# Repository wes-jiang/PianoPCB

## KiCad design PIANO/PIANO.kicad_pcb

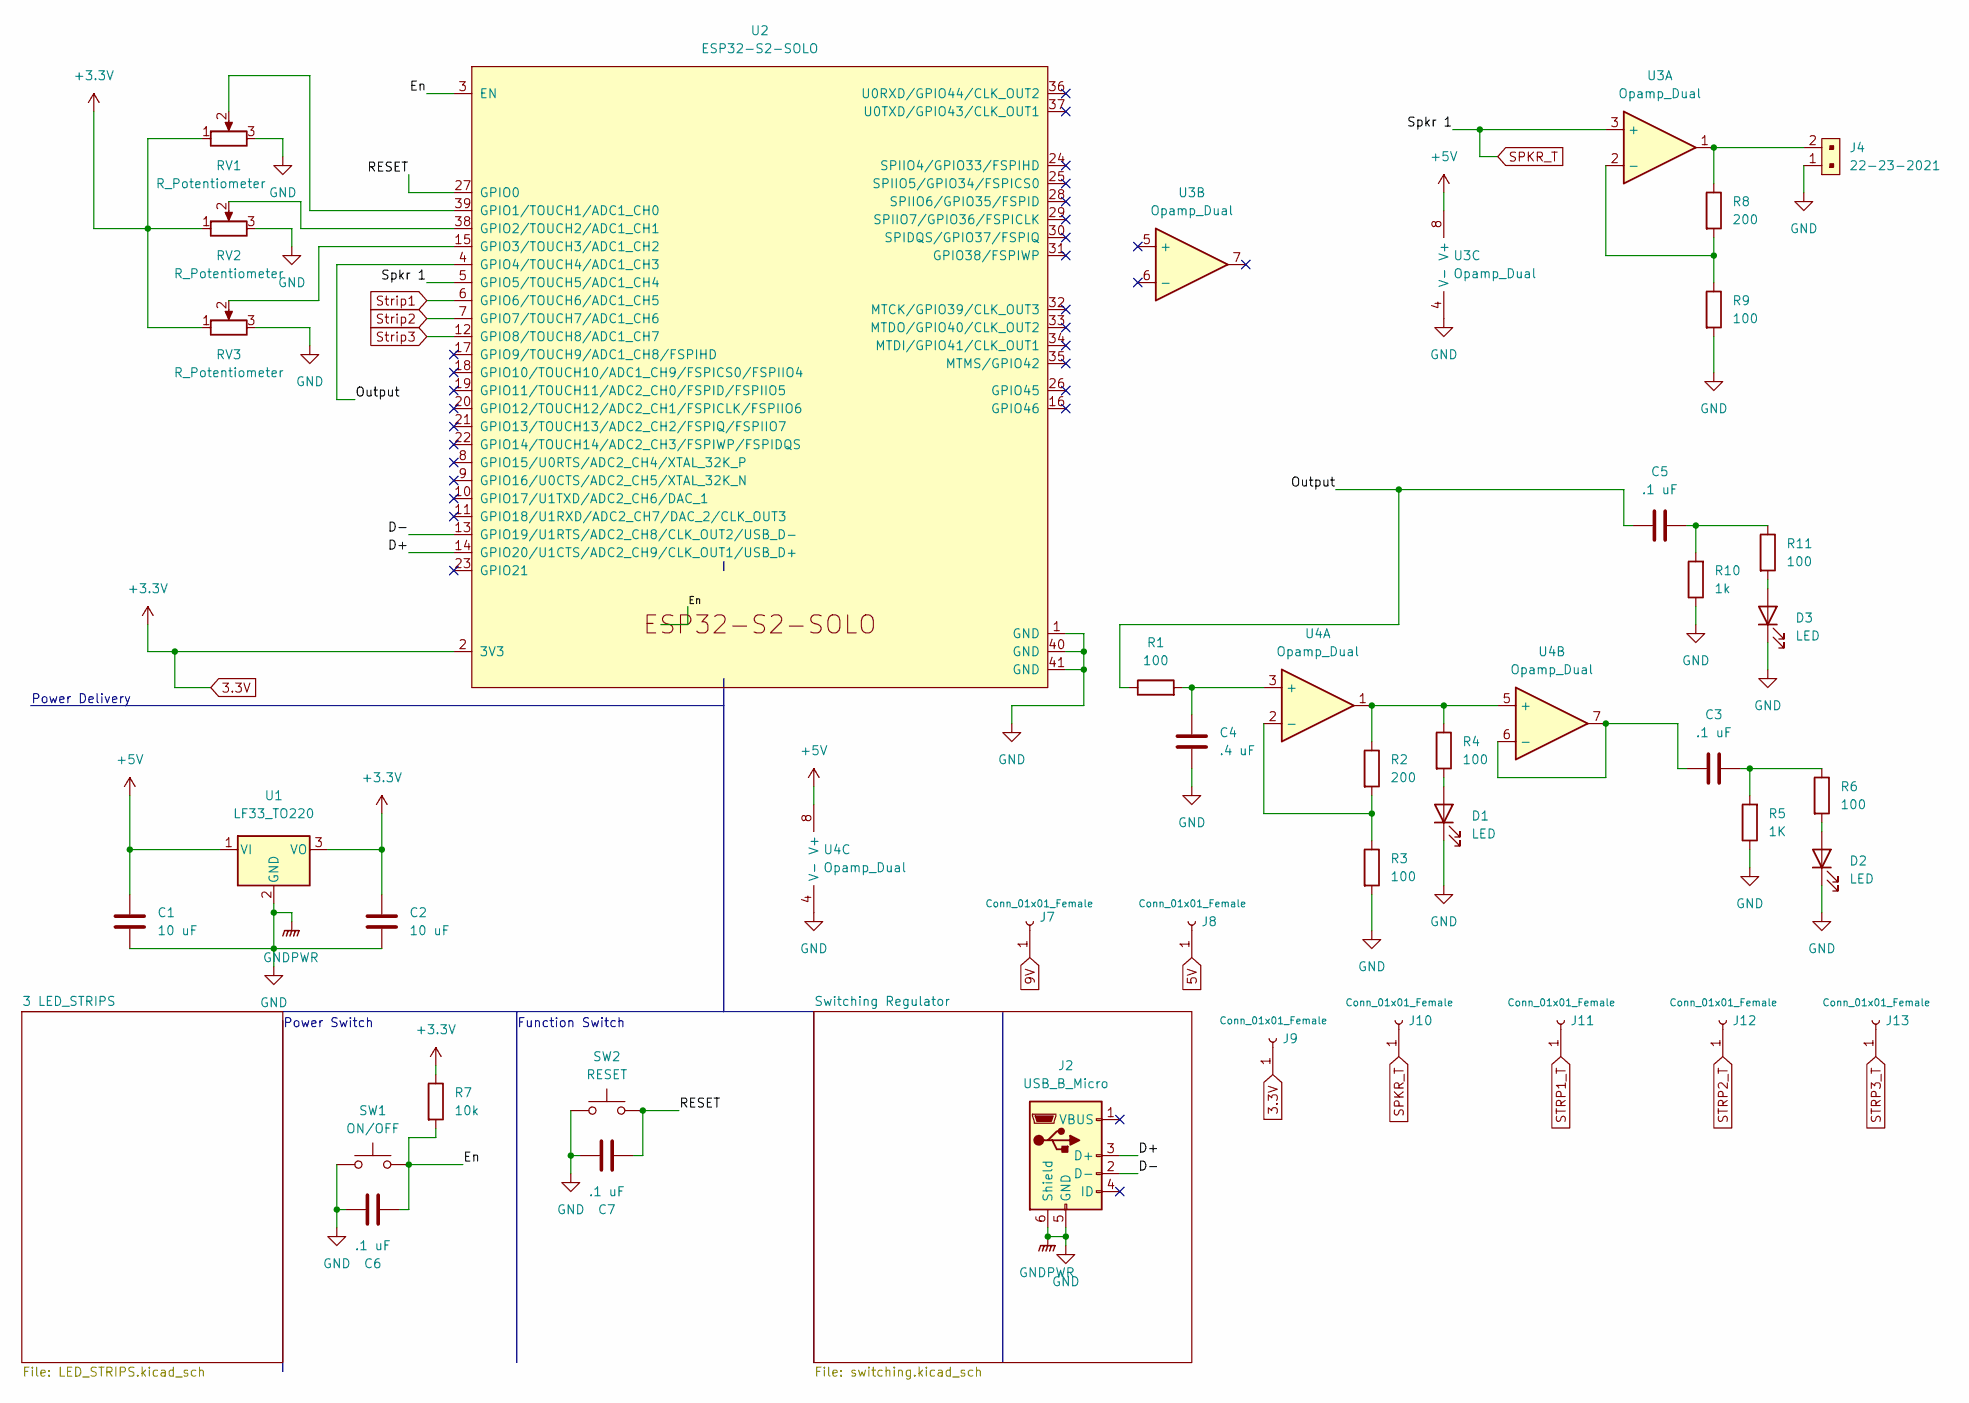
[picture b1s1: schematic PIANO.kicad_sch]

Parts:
C1, C2: 10 uF; C_0805_2012Metric
C3, C5, C6, C7: .1 uF; C_0603_1608Metric
C4: .4 uF; C_0603_1608Metric
D1, D2, D3: LED; LED_D5.0mm-3
J2: USB_B_Micro; USB_Micro-B_GCT_USB3076-30-A
J4: 22-23-2021; PinHeader_1x02_P2.54mm_Vertical; MPN 22-23-2021; Digi-Key_PN WM4200-ND
J7, J8, J9, J10, J11, J12, J13: Conn_01x01_Female; PinHeader_1x01_P2.54mm_Vertical
R1, R3, R4, R6, R9, R11: 100; R_0603_1608Metric
R2, R8: 200; R_0603_1608Metric
R5: 1K; R_0805_2012Metric
R7: 10k; R_0805_2012Metric
R10: 1k; R_0805_2012Metric
RV1, RV2, RV3: R_Potentiometer; Potentiometer_ACP_CA9-V10_Vertical
SW1: ON/OFF; SW_DPDT_CK_JS202011JCQN
SW2: RESET; SW_DPDT_CK_JS202011JCQN
U1: LF33_TO220; TO-220-3_Vertical
U2: ESP32-S2-SOLO
U3, U4: Opamp_Dual; SOIC127P600X175-8N

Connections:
3.3V: C2.1, J9.1, R7.1, RV1.1, RV2.1, RV3.1, U1.3 (VO), U2.2 (3V3)
5V: C1.1, J8.1, U1.1 (VI), U3.8 (V+), U4.8 (V+); also elsewhere on the board
9V: J7.1; also elsewhere on the board
/D+: J2.3 (D+), U2.14 (GPIO20/U1CTS/ADC2_CH9/CLK_OUT1/USB_D+)
/D-: J2.2 (D-), U2.13 (GPIO19/U1RTS/ADC2_CH8/CLK_OUT2/USB_D-)
/En: C6.2, R7.2, SW1.2, U2.3 (EN)
/IO0: C7.2, SW2.2, U2.27 (GPIO0)
/Output: C5.1, R1.1, U2.4 (GPIO4/TOUCH4/ADC1_CH3)
GND: C1.2, C2.2, C4.2, C6.1, C7.1, D1.1 (K), D2.1 (K), D3.1 (K), J2.5 (GND), J2.6 (Shield), J4.1, R3.2, R5.1, R9.2, R10.1, RV1.3, RV2.3, RV3.3, SW1.1, SW2.1, U1.2 (GND), U2.1 (GND), U2.40 (GND), U2.41 (GND), U3.4 (V-), U4.4 (V-); also elsewhere on the board
unnamed: C3.1, U4.6 (-), U4.7
unnamed: C3.2, R5.2, R6.1
unnamed: C4.1, R1.2, U4.3 (+)
unnamed: C5.2, R10.2, R11.1
unnamed: D1.2 (A), R4.2
unnamed: D2.2 (A), R6.2
unnamed: D3.2 (A), R11.2
unnamed: J4.2, R8.1, U3.1
unnamed: R2.1, R4.1, U4.1, U4.5 (+)
unnamed: R2.2, R3.1, U4.2 (-)
unnamed: R8.2, R9.1, U3.2 (-)
unnamed: RV1.2, U2.39 (GPIO1/TOUCH1/ADC1_CH0)
unnamed: RV2.2, U2.38 (GPIO2/TOUCH2/ADC1_CH1)
unnamed: RV3.2, U2.15 (GPIO3/TOUCH3/ADC1_CH2)
SPKR_T: J10.1, U2.5 (GPIO5/TOUCH5/ADC1_CH4), U3.3 (+)
STRP2_T: J12.1, U2.7 (GPIO7/TOUCH7/ADC1_CH6); also elsewhere on the board
STRP3_T: J13.1, U2.12 (GPIO8/TOUCH8/ADC1_CH7); also elsewhere on the board
Strip1: J11.1, U2.6 (GPIO6/TOUCH6/ADC1_CH5); also elsewhere on the board

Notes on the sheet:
Power Delivery
Power Switch
Function Switch

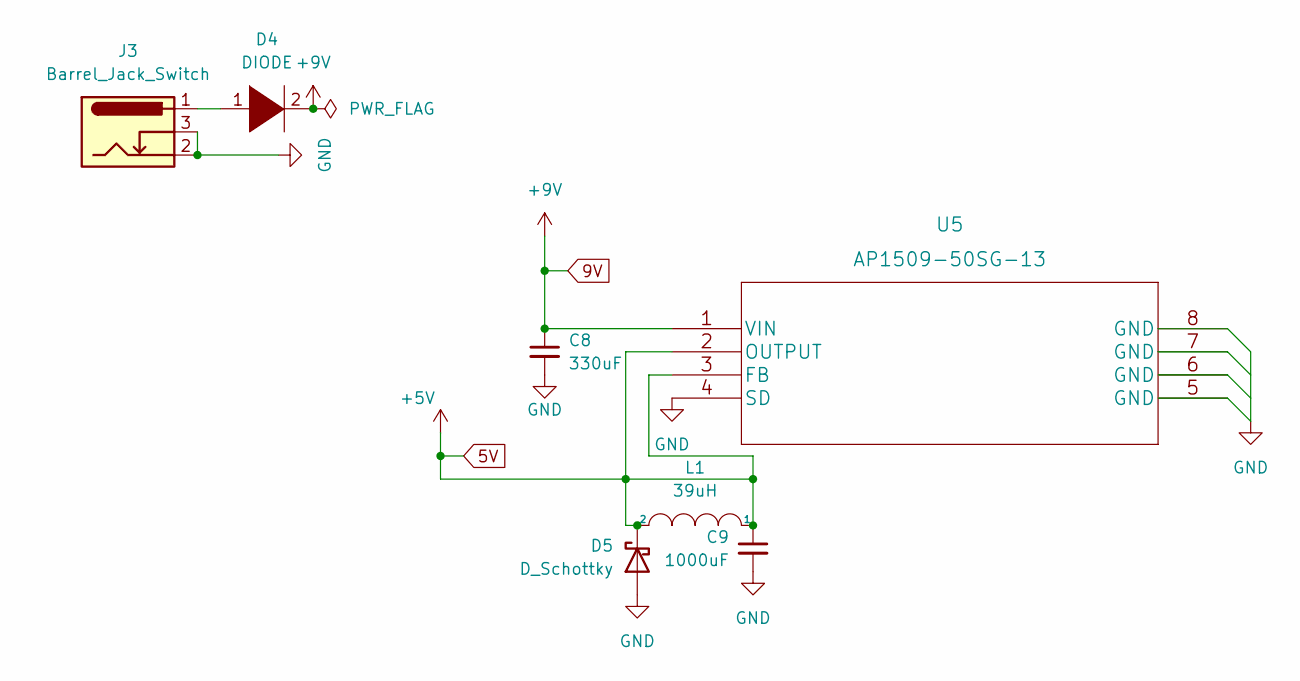
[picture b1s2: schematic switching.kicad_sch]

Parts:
C8: 330uF; C_1210_3225Metric
C9: 1000uF; C_Radial_D10.0mm_H16.0mm_P5.00mm
D4: DIODE; D_SOD-123F
D5: D_Schottky; D_SOD-123F
J3: Barrel_Jack_Switch; BarrelJack_Horizontal
L1: 39uH; L_10.4x10.4_H4.8
U5: AP1509-50SG-13; SOIC-8_3.9x4.9mm_P1.27mm

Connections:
5V: C9.1, D5.1 (K), L1.1, L1.2, U5.2 (OUTPUT), U5.3 (FB); also elsewhere on the board
9V: C8.1, D4.2 (A), U5.1 (VIN); also elsewhere on the board
GND: C8.2, C9.2, D5.2 (A), J3.2, J3.3, U5.4 (SD), U5.5 (GND), U5.6 (GND), U5.7 (GND), U5.8 (GND); also elsewhere on the board
unnamed: D4.1 (K), J3.1

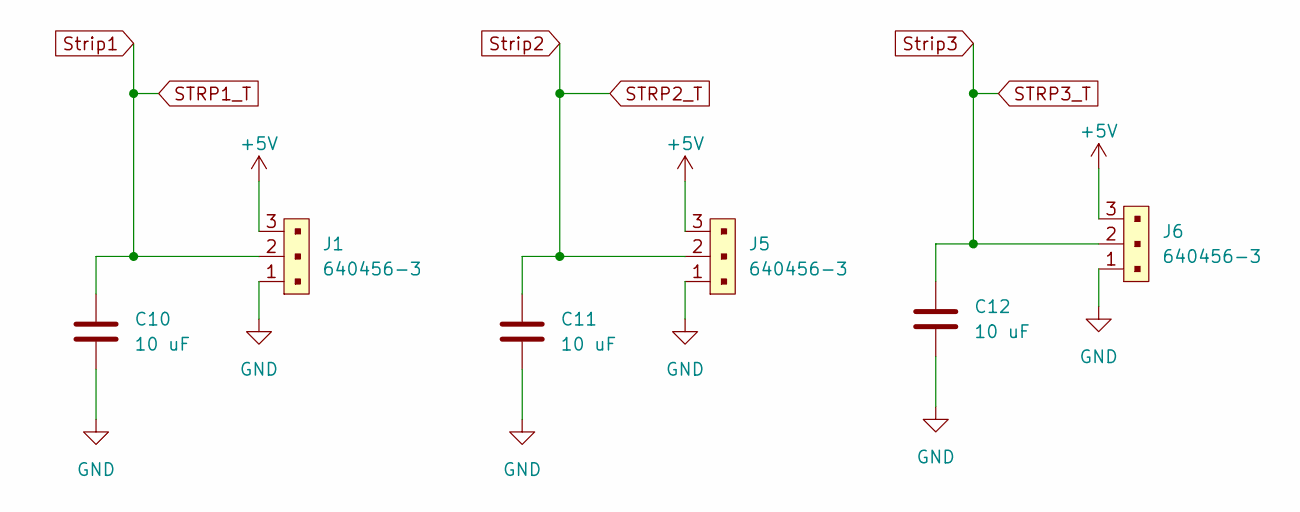
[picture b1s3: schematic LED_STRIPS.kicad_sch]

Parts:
C10, C11, C12: 10 uF; C_0805_2012Metric
J1, J5, J6: 640456-3; PinHeader_1x03_P2.54mm_Vertical; MPN 640456-3; Digi-Key_PN A19470-ND

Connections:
5V: J1.3, J5.3, J6.3; also elsewhere on the board
GND: C10.2, C11.2, C12.2, J1.1, J5.1, J6.1; also elsewhere on the board
STRP2_T: C11.1, J5.2; also elsewhere on the board
STRP3_T: C12.1, J6.2; also elsewhere on the board
Strip1: C10.1, J1.2; also elsewhere on the board

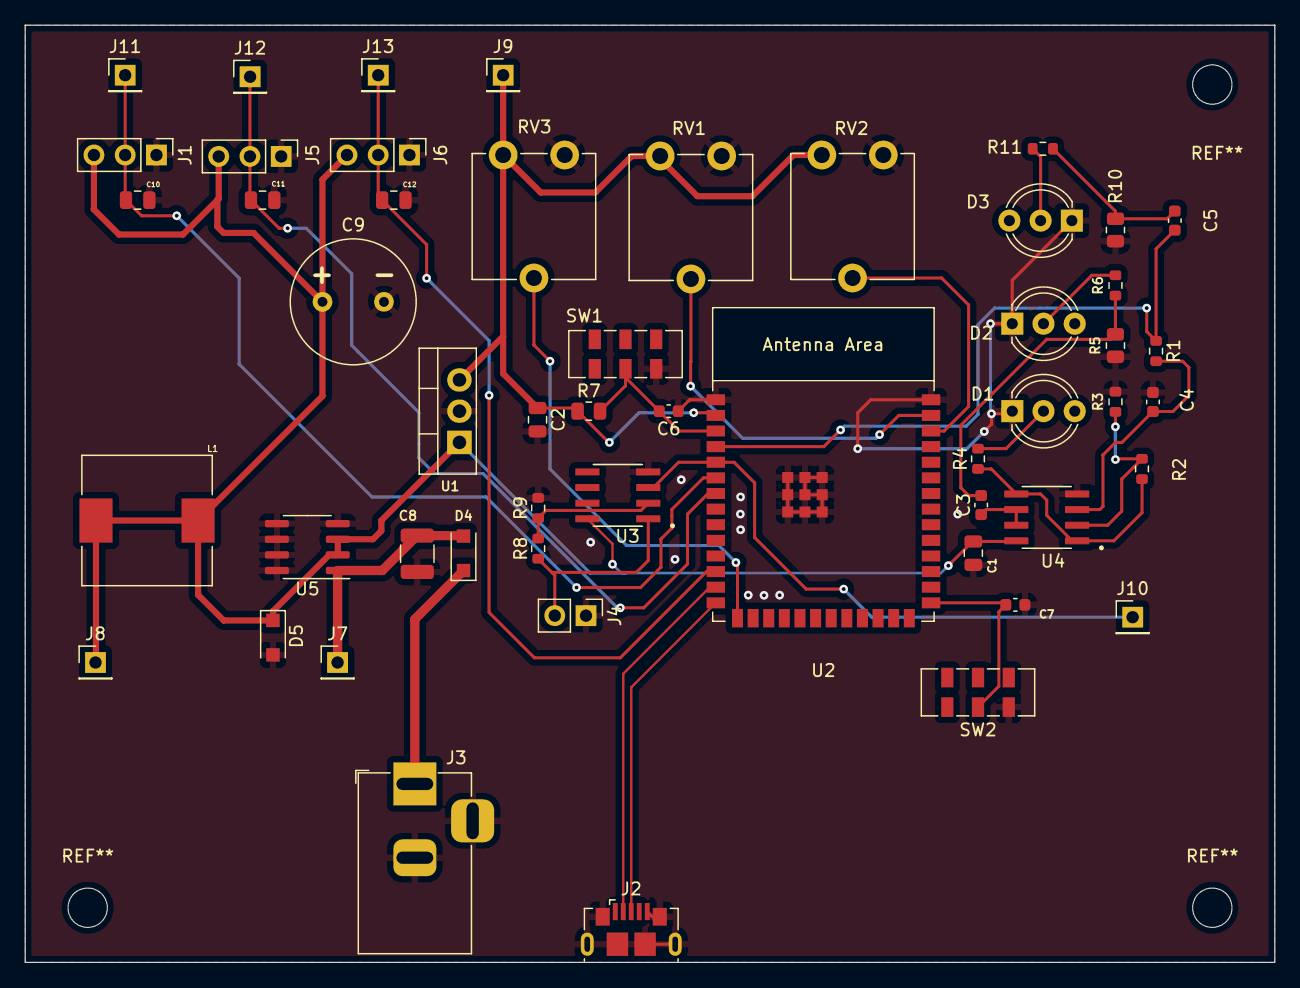
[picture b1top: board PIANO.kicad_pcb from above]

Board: 2 copper layers, 101.6 x 76.2 mm, 52 parts (0 on the bottom side), 28 nets.

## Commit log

2022-04-01 PCB SCHEMATIC and BOM
2022-04-07 dflskdjf
2022-04-08 During Class Commit
    This contains all changes before design review
2022-04-09 Final Handoff to Wesley
    Corrected units, created exclusion, thickened traces
2022-04-14 New Power Delivery
    Created new switching regulator and respective passives.
2022-04-15 added usb component
2022-04-15 added some stuff
2022-04-15 Bathroom Trip Commit
    Did the circuit for most of the regulator
2022-04-15 fixed mad errors'
2022-04-15 external spkr2
2022-04-15 try again
2022-04-15 added pin headers waiting for check
2022-04-15 need to final check
2022-04-15 task: move components
2022-04-15 Semi-Final Product
    Pin headers added, traces cleaned up, and figured out some funky grounding issues.
2022-04-15 added pos/neg
2022-04-15 Final Check from Elam
    Now Quality of Life and mounting holes remain.
2022-04-15 Pushing the Fiasco
    Strange reversions cause Git algorithm sucks
2022-04-16 fixed most things
